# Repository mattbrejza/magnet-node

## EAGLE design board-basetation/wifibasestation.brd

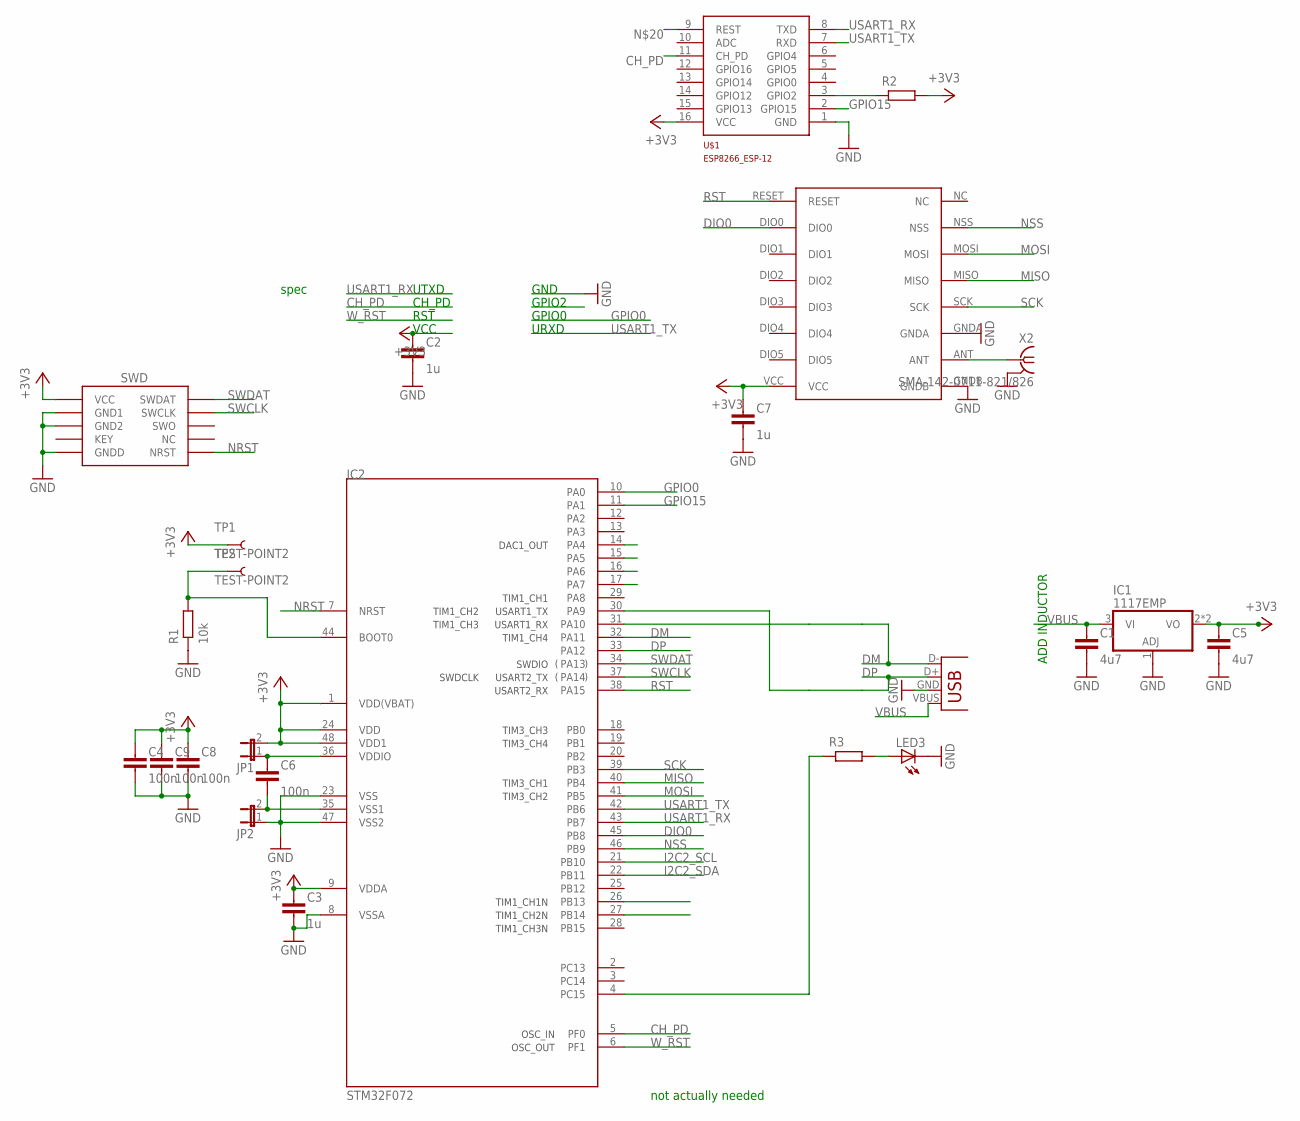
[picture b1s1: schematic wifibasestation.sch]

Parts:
C1: 4u7; C0603-N
C2, C3, C7: 1u; C0603-N
C4, C6, C8, C9: 100n; C0603-N
C5: 4u7; C0805-N
IC1: 1117EMP; SOT223
IC2: STM32F072; TQFP48
J1: SWD_SHROUD_SMD; SWD_SMD_SHROUD
JP1, JP2: JUMPER-2SMD-NC; SJ_2S
JP3: USB-A-H
LED3: LEDCHIP-LED0805; CHIP-LED0805
R1: 10k; R0603-N
R2, R3: RESISTOR0603-N; R0603-N
TP1, TP2: TEST-POINT2; PAD.02X.02
U$1: ESP8266_ESP-12; ESP8266-ESP12
U$2: RFM69HW; RFM
X2: SMA-142-0711-821/826; J502-ND-142-0711-821/826

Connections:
+3V3: C2.1, C3.1, C4.1, C5.1, C7.1, C8.1, C9.1, IC1.2 (VO), IC1.4 (VO), IC2.1 (VDD(VBAT)), IC2.9 (VDDA), IC2.24 (VDD), IC2.48 (VDD1), J1.1 (VCC), JP1.2, R2.2, TP1.P$1, U$1.16 (VCC), U$2.VCC
CH_PD: IC2.5 (PF0), U$1.11 (CH_PD)
DIO0: IC2.45 (PB8), U$2.DIO0
DM: IC2.31 (PA10), IC2.32 (PA11), JP3.D- (D+)
DP: IC2.30 (PA9), IC2.33 (PA12), JP3.D+ (D-)
GND: C1.2, C2.2, C3.2, C4.2, C5.2, C7.2, C8.2, C9.2, IC1.1 (ADJ), IC2.8 (VSSA), IC2.23 (VSS), IC2.47 (VSS2), J1.3 (GND1), J1.5 (GND2), J1.9 (GNDD), JP2.1, JP3.GND (VBUS), LED3.C, R1.1, U$1.1 (GND), U$2.GNDA, U$2.GNDB, X2.G@1 (2), X2.G@2 (2), X2.G@3 (2), X2.G@4 (2)
GPIO0: IC2.10 (PA0)
GPIO15: IC2.11 (PA1), U$1.2 (GPIO15)
I2C2_SCL: IC2.21 (PB10)
I2C2_SDA: IC2.22 (PB11)
MISO: IC2.40 (PB4), U$2.MISO
MOSI: IC2.41 (PB5), U$2.MOSI
unnamed: R2.1, U$1.3 (GPIO2)
unnamed: U$2.ANT, X2.1
unnamed: LED3.A, R3.2
unnamed: C6.1, IC2.36 (VDDIO), JP1.1
unnamed: C6.2, IC2.35 (VSS1), JP2.2
unnamed: IC2.44 (BOOT0), R1.2, TP2.P$1
unnamed: IC2.4 (PC15), R3.1
NRST: IC2.7 (NRST), J1.10 (NRST)
NSS: IC2.46 (PB9), U$2.NSS
RST: IC2.38 (PA15), U$2.RESET
SCK: IC2.39 (PB3), U$2.SCK
SWCLK: IC2.37 (PA14), J1.4 (SWCLK)
SWDAT: IC2.34 (PA13), J1.2 (SWDAT)
USART1_RX: IC2.43 (PB7), U$1.8 (TXD)
USART1_TX: IC2.42 (PB6), U$1.7 (RXD)
VBUS: C1.1, IC1.3 (VI), JP3.VBUS (GND)
W_RST: IC2.6 (PF1)

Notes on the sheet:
VCC
URXD
RST
CH_PD
UTXD
GPIO0
GPIO2
GND
not actually needed
spec
ADD INDUCTOR

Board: 2 copper layers, 24 parts (2 on the bottom side), 25 nets, no tracks yet.

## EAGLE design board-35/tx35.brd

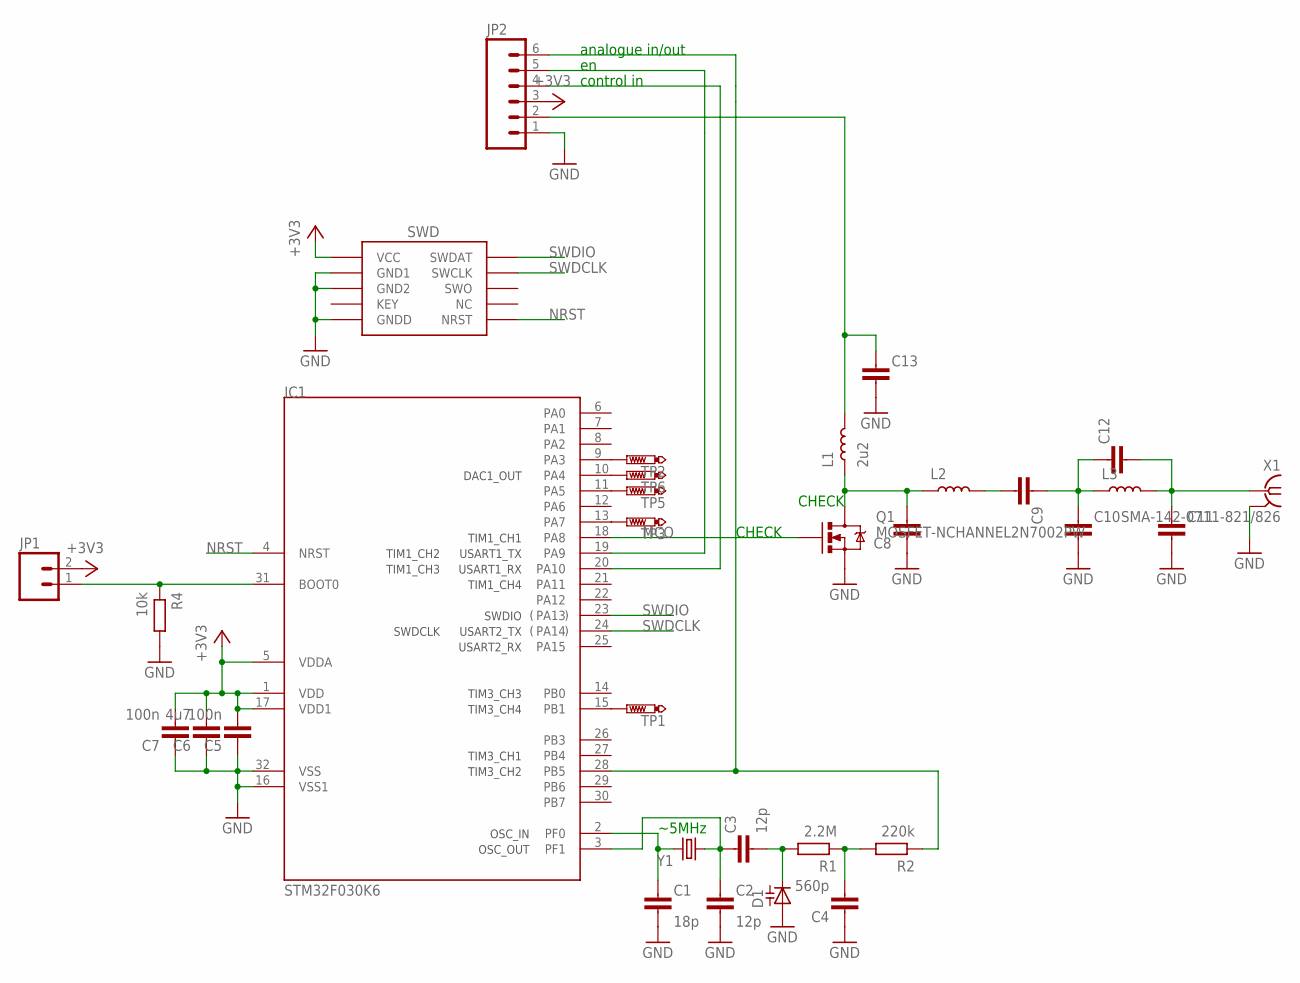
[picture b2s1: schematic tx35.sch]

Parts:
C1: 18p; C0603-N
C2, C3: 12p; C0603-N
C4: 560p; C0603-N
C5, C7: 100n; C0603-N
C6: 4u7; C0603-N
C8: CAPACITOR0603-N; C0603-N; FARNELL 2434613/2435457
C9, C10, C11, C12: CAPACITOR0603-N; C0603-N
C13: CAPACITOR0805-N; C0805-N
D1: DIODE_CAPACITANCE-SOD523; SOD523; FARNELL 1757783/(2443453)
IC1: STM32F030K6; TQFP32-08; FARNELL 2432085
J1: SWD_SHROUD; SWD_PTH_SHROUD
JP1: M02PTH; 1X02
JP2: M06SILK_FEMALE_PTH; 1X06
L1: 2u2; L0603-N; FARNELL 2215642
L2: INDUCTOR0603-N; L0603-N; FARNELL 1669538/(1711879)
L3: INDUCTOR0603-N; L0603-N
Q1: MOSFET-NCHANNEL2N7002PW; SOT323; FARNELL 1894713
R1: 2.2M; R0603-N
R2: 220k; R0603-N
R4: 10k; R0603-N
TP1, TP2, TP3, TP5, TP6: PTR1TP11R; TP11R
X1: SMA-142-0711-821/826; J502-ND-142-0711-821/826
Y1: CRYSTALHC49UV; HC49U-V; FARNELL 1666962/(1652566)

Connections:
+3V3: C5.2, C6.2, C7.2, IC1.1 (VDD), IC1.5 (VDDA), IC1.17 (VDD1), J1.1 (VCC), JP1.2, JP2.3
GND: C1.2, C2.2, C4.1, C5.1, C6.1, C7.1, C8.1, C10.2, C11.2, C13.2, D1.A, IC1.16 (VSS1), IC1.32 (VSS), J1.3 (GND1), J1.5 (GND2), J1.9 (GNDD), JP2.1, Q1.2 (S), R4.2, X1.G@1 (2), X1.G@2 (2), X1.G@3 (2), X1.G@4 (2)
MCO: IC1.18 (PA8), Q1.1 (G)
unnamed: C2.1, C3.1, IC1.3 (PF1), Y1.1
unnamed: C1.1, IC1.2 (PF0), Y1.2
unnamed: C3.2, D1.C, R1.2
unnamed: C4.2, R1.1, R2.2
unnamed: IC1.28 (PB5), JP2.6, R2.1
unnamed: C11.1, C12.2, L3.2, X1.1
unnamed: C13.1, JP2.2, L1.2
unnamed: C9.1, C10.1, C12.1, L3.1
unnamed: IC1.20 (PA10), JP2.4
unnamed: C9.2, L2.2
unnamed: C8.2, L1.1, L2.1, Q1.3 (D)
unnamed: IC1.19 (PA9), JP2.5
unnamed: IC1.31 (BOOT0), JP1.1, R4.1
unnamed: IC1.9 (PA3), TP2.TP
unnamed: IC1.15 (PB1), TP1.TP
unnamed: IC1.13 (PA7), TP3.TP
unnamed: IC1.11 (PA5), TP5.TP
unnamed: IC1.10 (PA4), TP6.TP
NRST: IC1.4 (NRST), J1.10 (NRST)
SWDCLK: IC1.24 (PA14), J1.4 (SWCLK)
SWDIO: IC1.23 (PA13), J1.2 (SWDAT)

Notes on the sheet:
~5MHz
CHECK
analogue in/out
control in

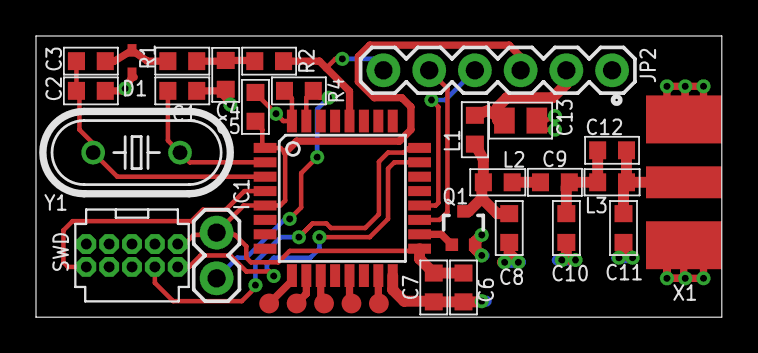
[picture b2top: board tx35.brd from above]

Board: 2 copper layers, 38.1 x 15.6 mm, 32 parts (0 on the bottom side), 24 nets.

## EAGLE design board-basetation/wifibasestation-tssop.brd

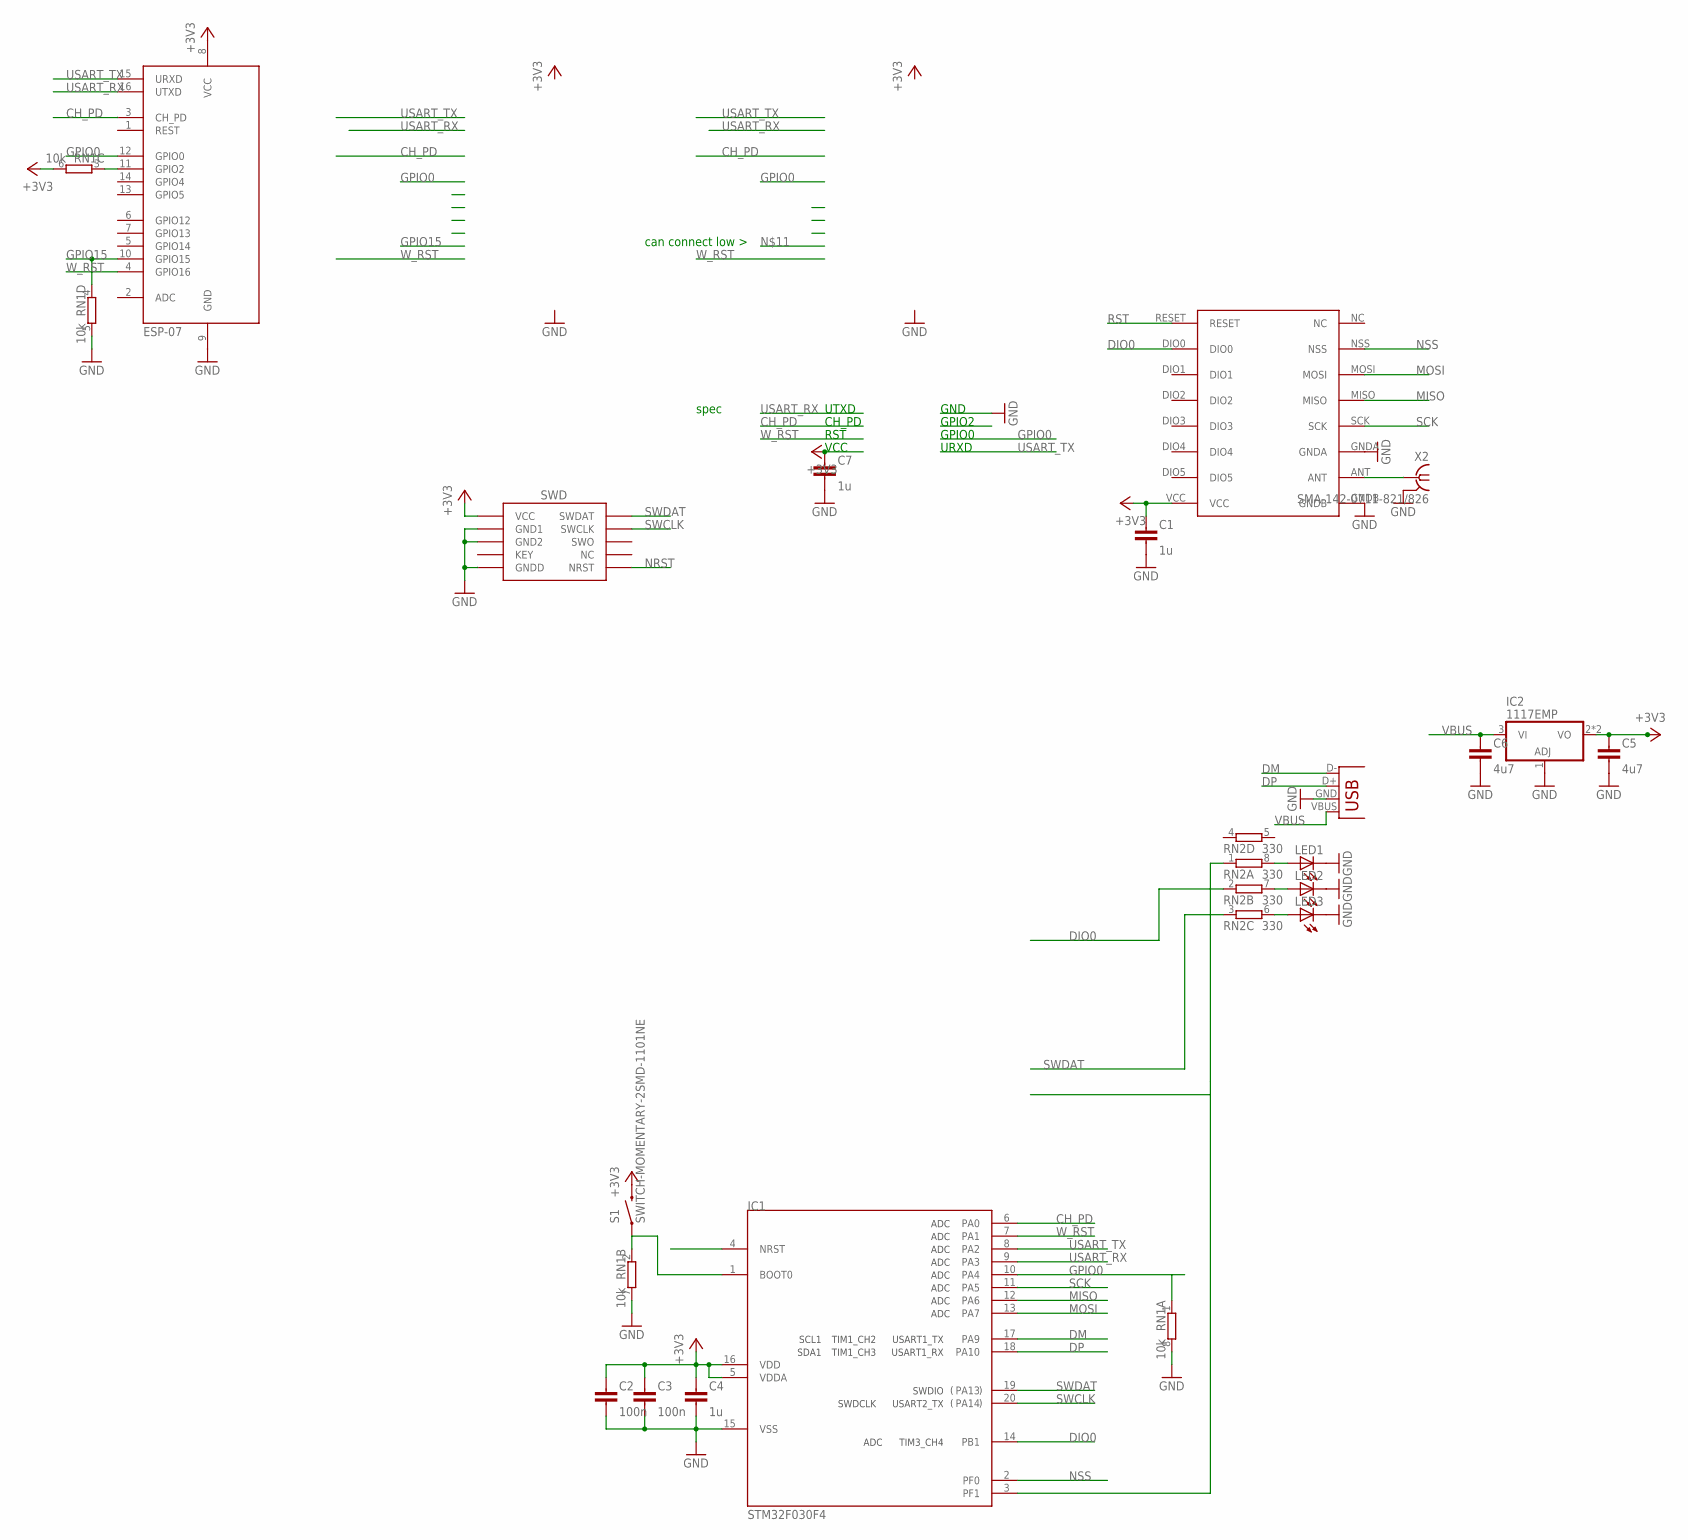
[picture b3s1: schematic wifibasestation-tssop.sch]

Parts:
C1, C4, C7: 1u; C0603-N
C2, C3: 100n; C0603-N
C5: 4u7; C0805-N
C6: 4u7; C0603-N
IC1: STM32F030F4; TSSOP20
IC2: 1117EMP; SOT223
J1: SWD_SHROUD_SMD; SWD_SMD_SHROUD
JP1: USB-A-H
LED1, LED2, LED3: LEDCHIP-LED0805; CHIP-LED0805
RN1: 10k; EXB38V
RN2: 330; EXB38V
S1: SWITCH-MOMENTARY-2SMD-1101NE; TACTILE-SWITCH-1101NE
U$1: RFM69HW; RFM
X1: ESP-07
X2: SMA-142-0711-821/826; J502-ND-142-0711-821/826

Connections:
+3V3: C1.1, C2.1, C3.1, C4.1, C5.1, C7.1, IC1.5 (VDDA), IC1.16 (VDD), IC2.2 (VO), IC2.4 (VO), J1.1 (VCC), RN1.6 (2), S1.2, U$1.VCC, X1.8 (VCC)
CH_PD: IC1.6 (PA0), X1.3 (CH_PD)
DIO0: IC1.14 (PB1), RN2.2 (1), U$1.DIO0
DM: IC1.17 (PA9), JP1.D- (D+)
DP: IC1.18 (PA10), JP1.D+ (D-)
GND: C1.2, C2.2, C3.2, C4.2, C5.2, C6.2, C7.2, IC1.15 (VSS), IC2.1 (ADJ), J1.3 (GND1), J1.5 (GND2), J1.9 (GNDD), JP1.GND (VBUS), LED1.C, LED2.C, LED3.C, RN1.5 (2), RN1.7 (2), RN1.8 (2), U$1.GNDA, U$1.GNDB, X1.9 (GND), X2.G@1 (2), X2.G@2 (2), X2.G@3 (2), X2.G@4 (2)
GPIO0: IC1.10 (PA4), RN1.1, X1.12 (GPIO0)
GPIO15: RN1.4 (1), X1.10 (GPIO15)
MISO: IC1.12 (PA6), U$1.MISO
MOSI: IC1.13 (PA7), U$1.MOSI
unnamed: IC1.1 (BOOT0), RN1.2 (1), S1.1
unnamed: U$1.ANT, X2.1
unnamed: RN1.3 (1), X1.11 (GPIO2)
unnamed: LED1.A, RN2.8 (2)
unnamed: LED2.A, RN2.7 (2)
unnamed: LED3.A, RN2.6 (2)
unnamed: IC1.3 (PF1), RN2.1
NRST: IC1.4 (NRST), J1.10 (NRST)
NSS: IC1.2 (PF0), U$1.NSS
RST: U$1.RESET
SCK: IC1.11 (PA5), U$1.SCK
SWCLK: IC1.20 (PA14), J1.4 (SWCLK)
SWDAT: IC1.19 (PA13), J1.2 (SWDAT), RN2.3 (1)
USART_RX: IC1.9 (PA3), X1.16 (UTXD)
USART_TX: IC1.8 (PA2), X1.15 (URXD)
VBUS: C6.1, IC2.3 (VI), JP1.VBUS (GND)
W_RST: IC1.7 (PA1), X1.4 (GPIO16)

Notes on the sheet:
VCC
URXD
RST
CH_PD
UTXD
GPIO0
GPIO2
GND
spec
can connect low >

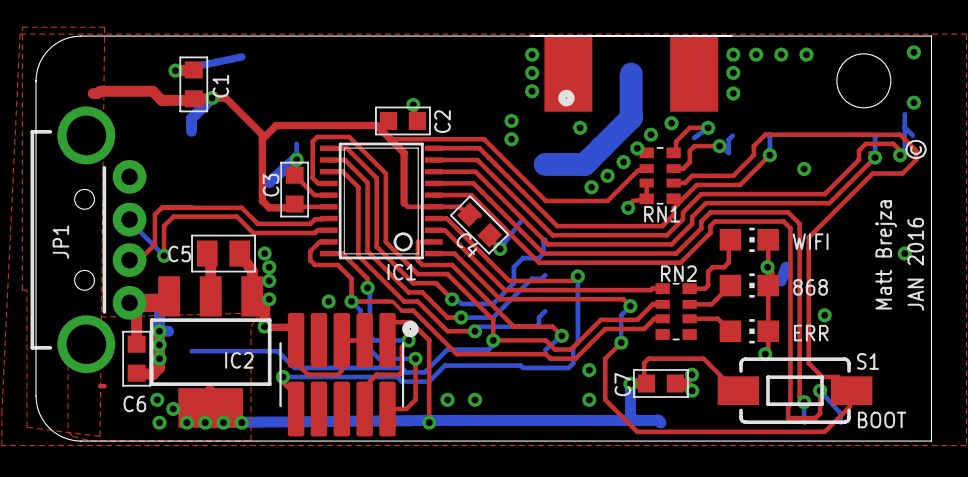
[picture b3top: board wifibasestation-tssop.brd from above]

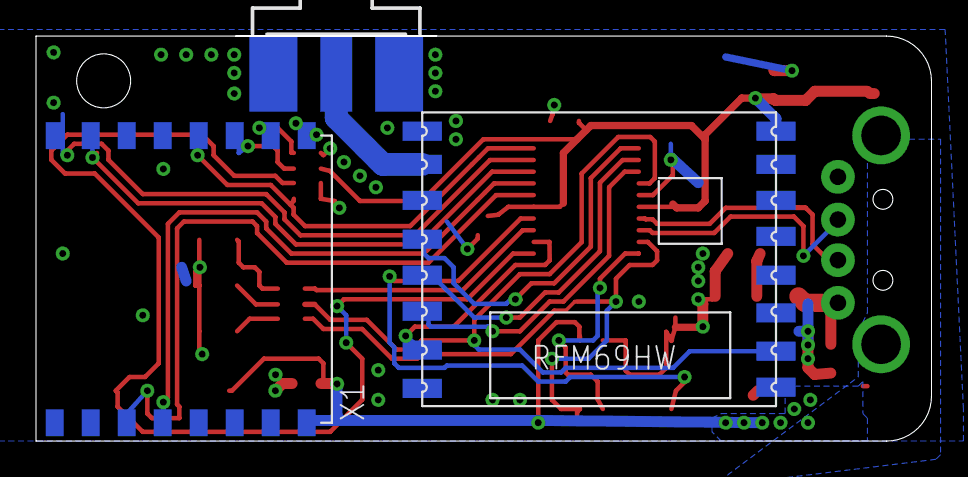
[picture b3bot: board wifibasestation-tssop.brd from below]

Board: 2 copper layers, 49.8 x 22.5 mm, 20 parts (3 on the bottom side), 26 nets.

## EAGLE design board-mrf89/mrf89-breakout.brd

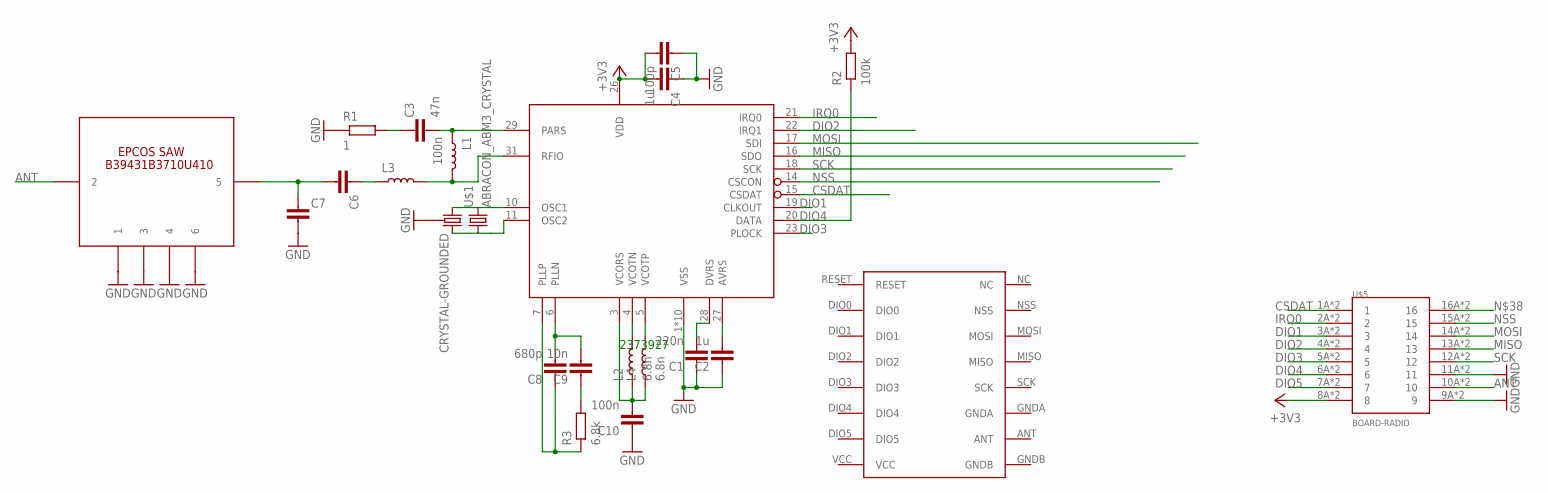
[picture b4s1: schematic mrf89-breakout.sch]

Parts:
C1: 220n; C0603-N
C2, C4: 1u; C0603-N
C3: 47n; C0603-N
C5: 100p; C0603-N
C6, C7: CAPACITOR0603-N; C0603-N
C8: 680p; C0603-N
C9: 10n; C0603-N
C10: 100n; C0603-N
IC1: MRF89XA; QFN32
L1: 100n; L0603-N
L2, L4: 6.8n; L0402-N
L3: INDUCTOR0402-N; L0402-N
R1: 1; R0603-N
R2: 100k; R0603-N
R3: 6.8k; R0603-N
U$1: ABRACON_ABM3_CRYSTAL
U$2: EPCOS_SAW_FILTER
U$3: RFM69HW; RFM
U$4: CRYSTAL-GROUNDED; CRYSTAL-SMD-5X3
U$5: BOARD-RADIO

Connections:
+3V3: C4.2, C5.2, IC1.26 (VDD), R2.2, U$5.8A (8), U$5.8B (8)
ANT: U$2.P$2 (2), U$5.10A (10), U$5.10B (10)
CSDAT: IC1.15 (CSDAT), U$5.1A (1), U$5.1B (1)
DIO1: IC1.19 (CLKOUT), U$5.3A (3), U$5.3B (3)
DIO2: IC1.22 (IRQ1), U$5.4A (4), U$5.4B (4)
DIO3: IC1.23 (PLOCK), U$5.5A (5), U$5.5B (5)
DIO4: IC1.20 (DATA), R2.1, U$5.6A (6), U$5.6B (6)
DIO5: U$5.7A (7), U$5.7B (7)
GND: C1.1, C2.1, C4.1, C5.1, C7.2, C10.1, IC1.1 (VSS), IC1.2 (VSS), IC1.8 (VSS), IC1.9 (VSS), IC1.12 (VSS), IC1.24 (VSS), IC1.25 (VSS), IC1.30 (VSS), IC1.32 (VSS), IC1.EXP (VSS), R1.1, U$2.P$1 (1), U$2.P$3 (3), U$2.P$4 (4), U$2.P$6 (6), U$4.2 (3), U$4.4 (3), U$5.9A (9), U$5.9B (9), U$5.11A (11), U$5.11B (11)
IRQ0: IC1.21 (IRQ0), U$5.2A (2), U$5.2B (2)
MISO: IC1.16 (SDO), U$5.13A (13), U$5.13B (13)
MOSI: IC1.17 (SDI), U$5.14A (14), U$5.14B (14)
unnamed: C1.2, IC1.28 (DVRS)
unnamed: C2.2, IC1.27 (AVRS)
unnamed: C3.2, IC1.29 (PARS), L1.1
unnamed: IC1.31 (RFIO), L1.2, L3.2
unnamed: C6.1, L3.1
unnamed: C6.2, C7.1, U$2.P$5 (5)
unnamed: C8.1, IC1.7 (PLLP), R3.1
unnamed: C8.2, C9.2, IC1.6 (PLLN)
unnamed: C9.1, R3.2
unnamed: IC1.4 (VCOTN), L2.2
unnamed: IC1.5 (VCOTP), L4.2
unnamed: C10.2, IC1.3 (VCORS), L2.1, L4.1
unnamed: C3.1, R1.2
unnamed: IC1.10 (OSC1), U$1.P$2 (2), U$4.3 (1)
unnamed: IC1.11 (OSC2), U$1.P$1 (1), U$4.1 (2)
unnamed: U$5.16A (16), U$5.16B (16)
NSS: IC1.14 (CSCON), U$5.15A (15), U$5.15B (15)
SCK: IC1.18 (SCK), U$5.12A (12), U$5.12B (12)

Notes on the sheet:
2373927

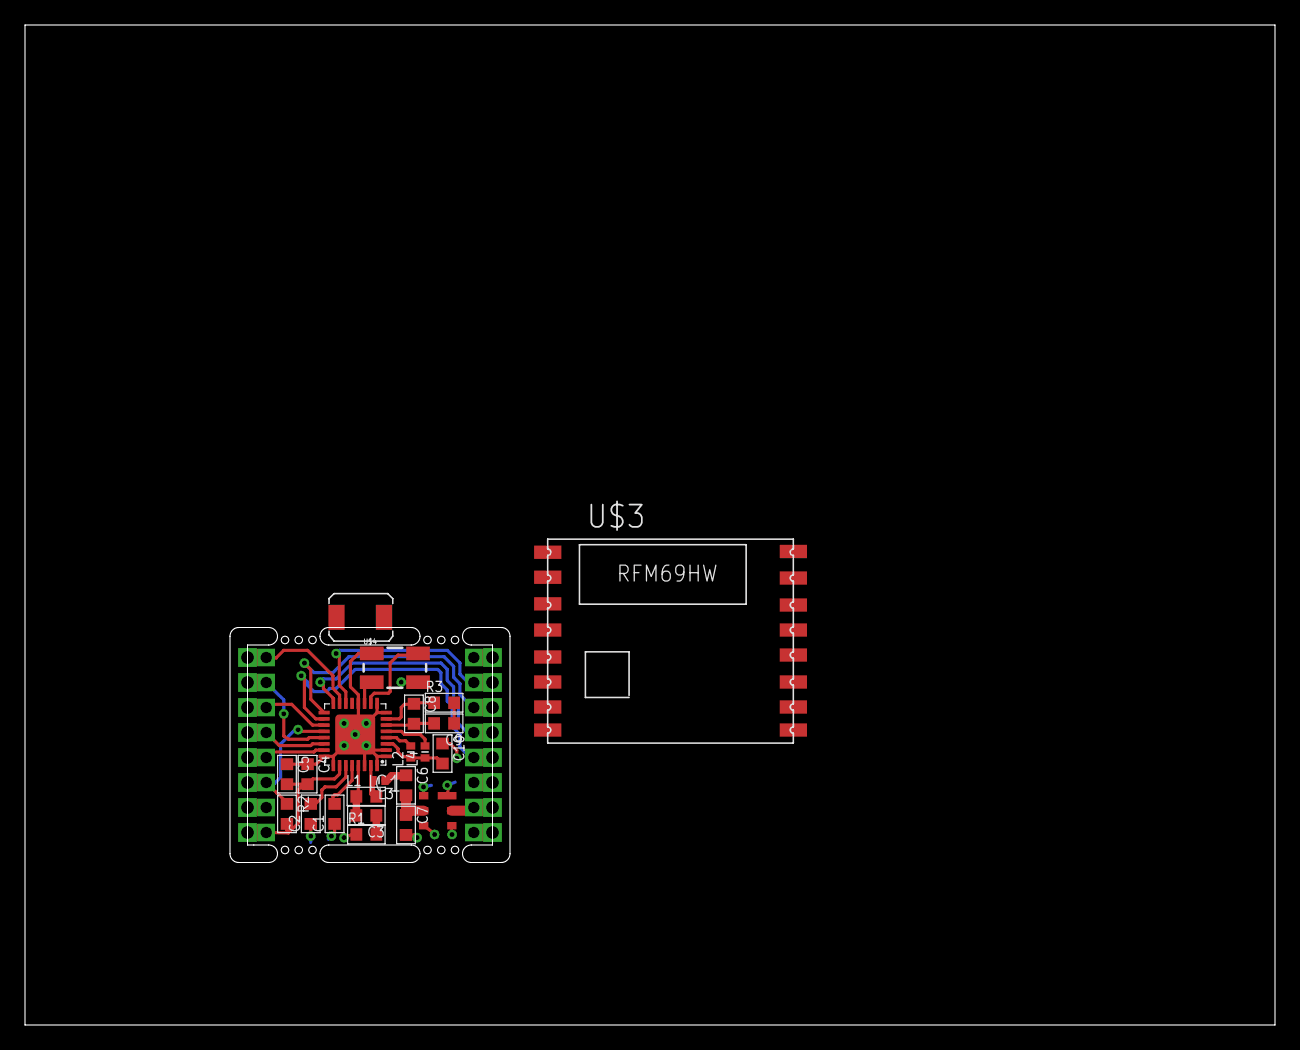
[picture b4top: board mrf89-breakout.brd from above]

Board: 2 copper layers, 100.0 x 80.0 mm, 24 parts (0 on the bottom side), 30 nets.

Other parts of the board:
U$6: BOARD-RADIO-CUTOUT

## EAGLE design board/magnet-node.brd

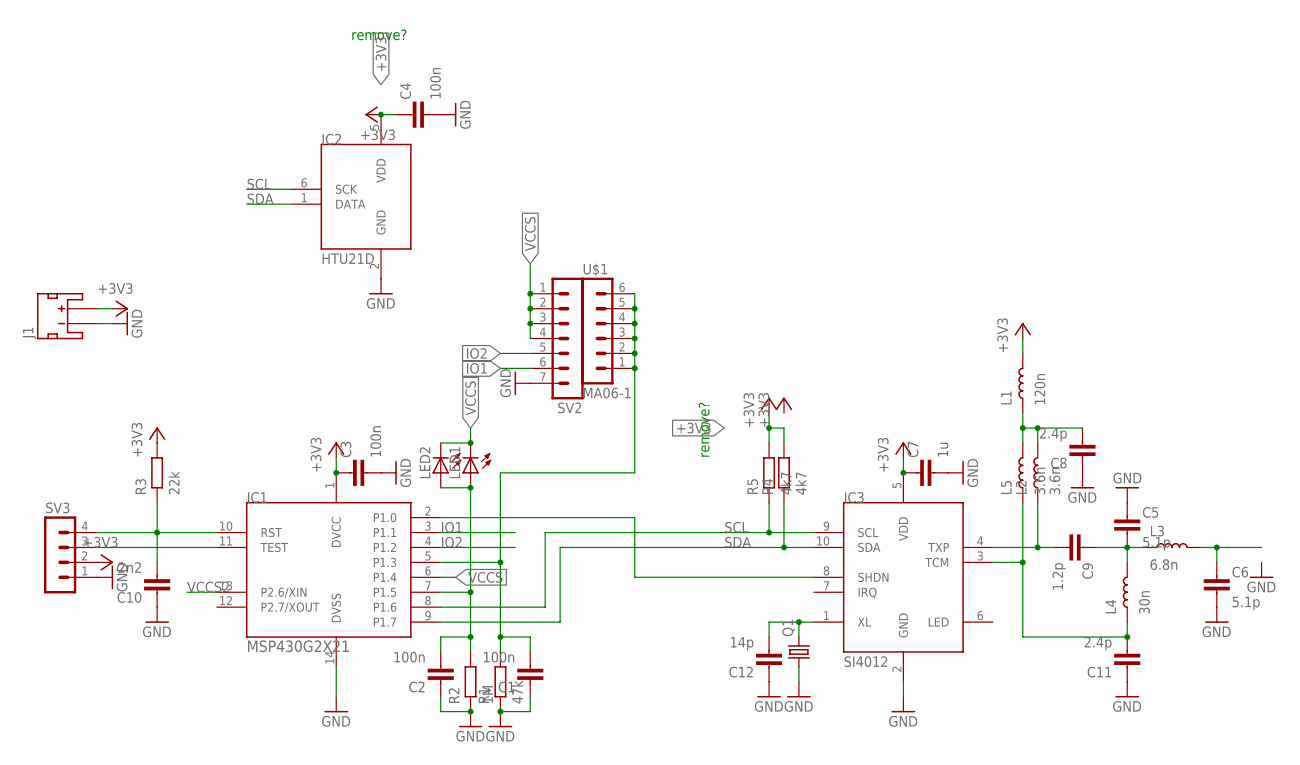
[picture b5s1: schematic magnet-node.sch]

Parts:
C1, C2, C3, C4: 100n; C0603-N
C5, C6: 5.1p; C0603-N
C7: 1u; C0603-N
C8, C11: 2.4p; C0603-N
C9: 1.2p; C0603-N
C10: 2n2; C0603-N
C12: 14p; C0603-N
IC1: MSP430G2X21; TSSOP14
IC2: HTU21D; DFN6-L
IC3: SI4012; MSOP10
J1: JST_2MM_MALE_TH; JST-2-TH
L1: 120n; L0603-N
L2, L5: 3.6n; L0402-N
L3: 6.8n; L0402-N
L4: 30n; L0402-N
LED1, LED2: LEDSMT1206; 1206
Q1: CRYSTALHC49S; HC49/S
R1: 47k; R0603-N
R2: 1M; R0603-N
R3: 22k; R0603-N
R4, R5: 4k7; R0603-N
SV2: MA07-1S; MA07-1-SMD
SV3: MA04-1E; EDGE_4
U$1: MA06-1; MA06-1-SMD

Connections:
+3V3: C3.1, C4.1, C7.1, IC1.1 (DVCC), IC2.5 (VDD), IC3.5 (VDD), J1.1 (+), L1.2, R3.2, R4.2, R5.2, SV3.2
GND: C1.1, C2.1, C3.2, C4.2, C5.1, C6.2, C7.2, C8.1, C10.1, C11.1, C12.1, IC1.14 (DVSS), IC2.2 (GND), IC3.2 (GND), J1.2 (-), Q1.1, R1.1, R2.1, SV2.7, SV3.1
IO1: IC1.3 (P1.1), SV2.6
IO2: IC1.4 (P1.2), SV2.5
unnamed: IC1.2 (P1.0), IC3.8 (SHDN)
unnamed: IC1.11 (TEST), SV3.3
unnamed: C8.2, L1.1, L2.2, L5.2
unnamed: C12.2, IC3.1 (XL), Q1.2
unnamed: C5.2, C9.1, L3.1, L4.2
unnamed: C11.2, IC3.3 (TCM), L4.1, L5.1
unnamed: C9.2, IC3.4 (TXP), L2.1
unnamed: C6.1, L3.2
unnamed: C1.2, IC1.5 (P1.3), R1.2, U$1.1, U$1.2, U$1.3, U$1.4, U$1.5, U$1.6
unnamed: C2.2, IC1.7 (P1.5), LED1.A, LED2.A, R2.2
unnamed: C10.2, IC1.10 (RST), R3.1, SV3.4
SCL: IC1.8 (P1.6), IC2.6 (SCK), IC3.9 (SCL), R5.1
SDA: IC1.9 (P1.7), IC2.1 (DATA), IC3.10 (SDA), R4.1
VCCS: IC1.6 (P1.4), LED1.C, LED2.C, SV2.1, SV2.2, SV2.3, SV2.4
VCCS2: IC1.13 (P2.6/XIN)

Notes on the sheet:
remove?

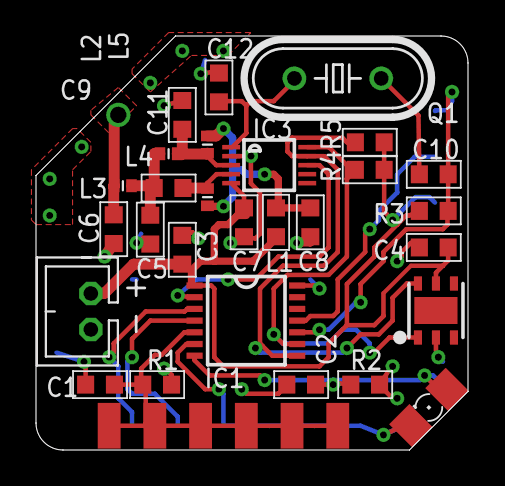
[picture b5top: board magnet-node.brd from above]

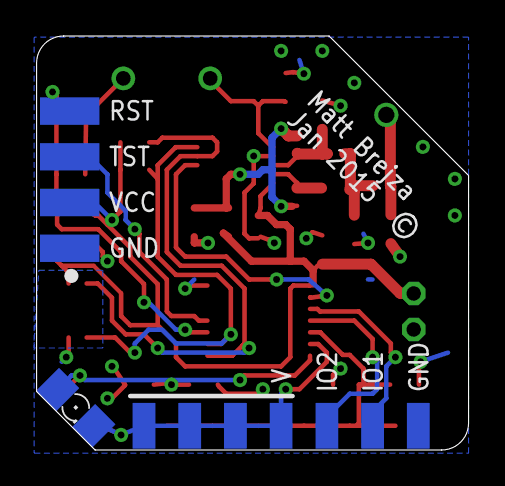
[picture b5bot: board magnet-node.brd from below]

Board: 2 copper layers, 24.0 x 23.0 mm, 32 parts (3 on the bottom side), 18 nets.

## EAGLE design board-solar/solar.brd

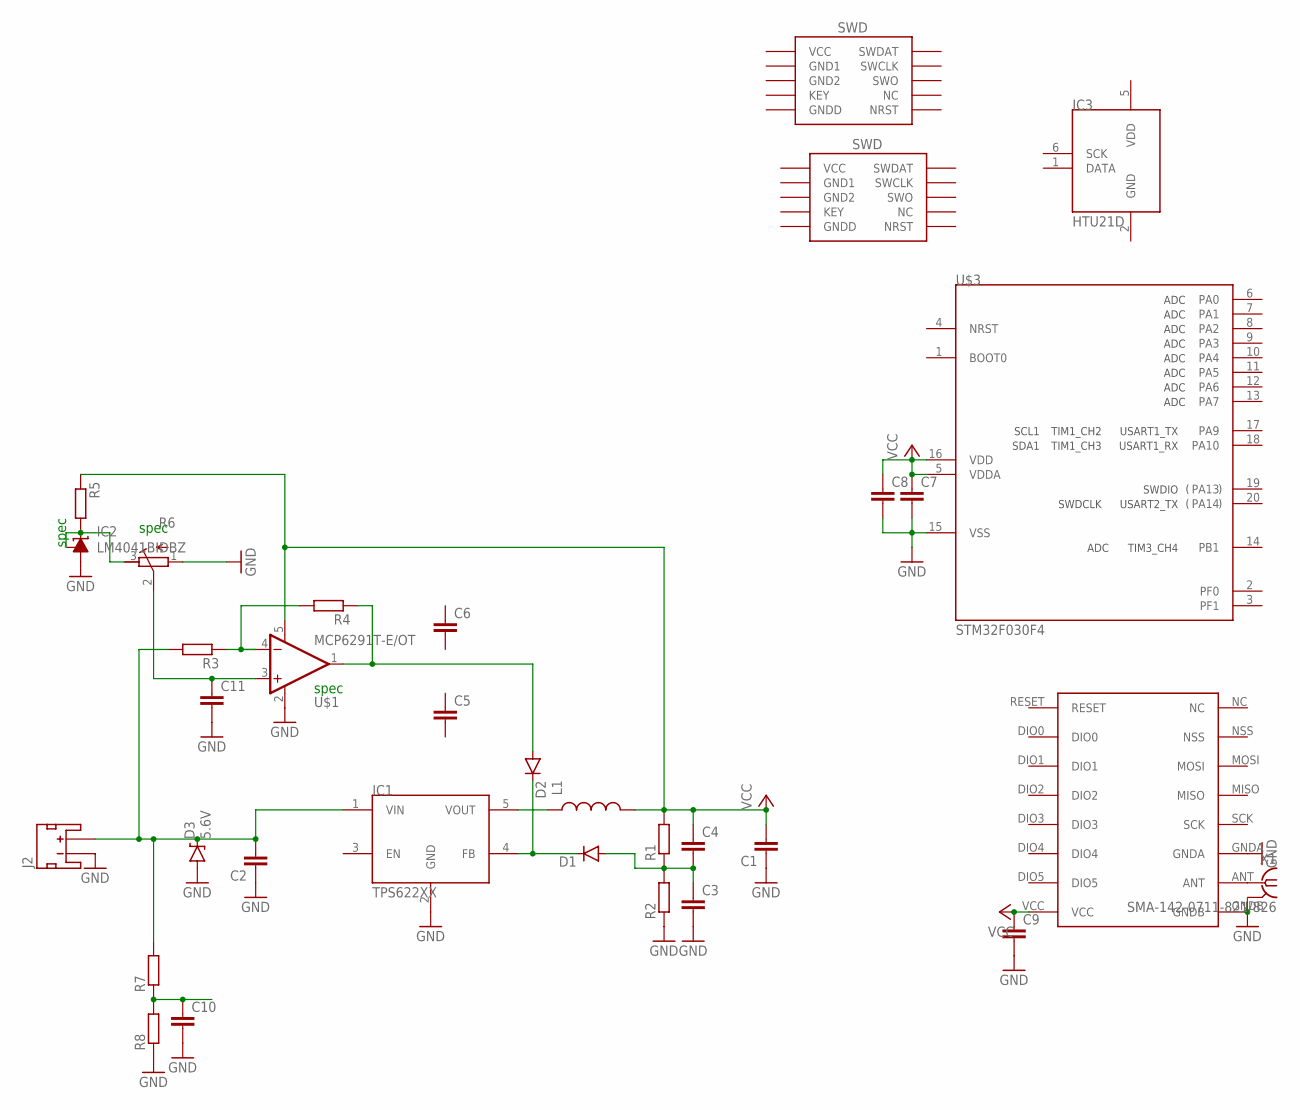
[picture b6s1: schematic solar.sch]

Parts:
C1, C2: C-EUC0805; C0805
C3, C4, C5, C6, C7, C8, C9, C10, C11: C-EUC0603; C0603
D1, D2: 250mA/100V; SOD-323
D3: 5.6V; SOD-323
IC1: TPS622XX; SOT23-5L
IC2: LM4041BIDBZ; DBZ_R-PDSO-G3
IC3: HTU21D; DFN6-L
J1: SWD_SHROUD_SMD; SWD_SMD_SHROUD
J2: JST_2MM_MALE; JST-2-SMD
J3: SWD_SHROUD; SWD_PTH_SHROUD
L1: INDUCTOR1007; 1007
R1, R2, R3, R4, R5, R7, R8: R-EU_R0603; R0603
R6: R-TRIMM3103; RTRIM3103
U$1: MCP6291T-E/OT; SOT23-5
U$3: STM32F030F4; TSSOP20
U$4: RFM69HW; RFM
X1: SMA-142-0711-821/826; J502-ND-142-0711-821/826

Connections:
GND: C1.1, C2.1, C3.2, C7.2, C8.2, C9.2, C10.2, C11.2, D3.A, IC1.2 (GND), IC2.3 (A), J2.1 (-), R2.1, R6.1 (E), R8.1, U$1.2 (V-), U$3.15 (VSS), U$4.GNDA, U$4.GNDB, X1.G@1 (2), X1.G@2 (2), X1.G@3 (2), X1.G@4 (2)
GND1: J1.3 (GND1), J3.3 (GND1)
GND2: J1.5 (GND2), J3.5 (GND2)
GNDD: J1.9 (GNDD), J3.9 (GNDD)
unnamed: C3.1, C4.2, D1.A, R1.1, R2.2
unnamed: IC1.5 (VOUT), L1.1
unnamed: D1.C, D2.C, IC1.4 (FB)
unnamed: C2.2, D3.C, IC1.1 (VIN), J2.2 (+), R3.2, R7.2
unnamed: D2.A, R4.1, U$1.1 (OUT)
unnamed: R3.1, R4.2, U$1.4 (-IN)
unnamed: C11.1, R6.2 (S), U$1.3 (+IN)
unnamed: U$4.ANT, X1.1
unnamed: IC2.1 (FB), IC2.2 (C), R5.2, R6.3 (A)
unnamed: C10.1, R7.1, R8.2
VCC: C1.2, C4.1, C7.1, C8.1, C9.1, J1.1 (VCC), J3.1 (VCC), L1.2, R1.2, R5.1, U$1.5 (V+), U$3.5 (VDDA), U$3.16 (VDD), U$4.VCC

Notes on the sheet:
spec

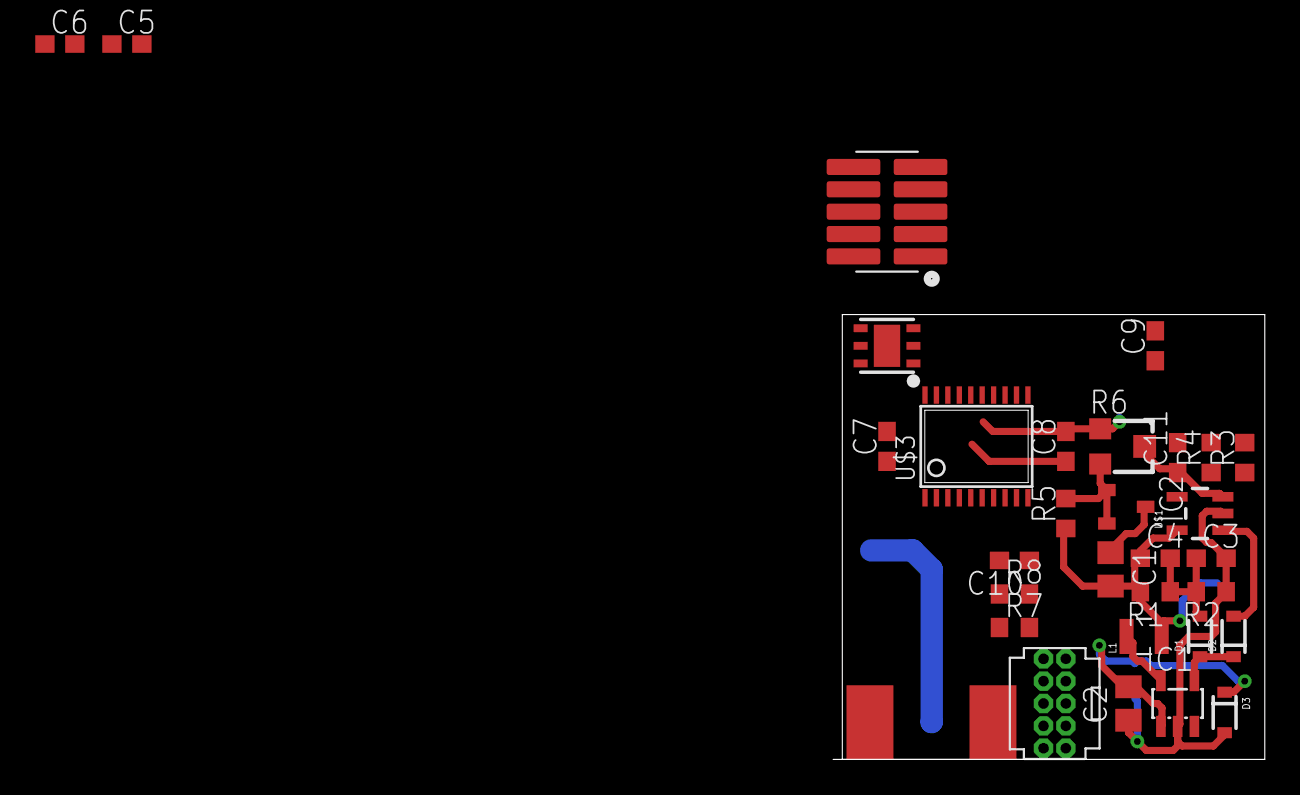
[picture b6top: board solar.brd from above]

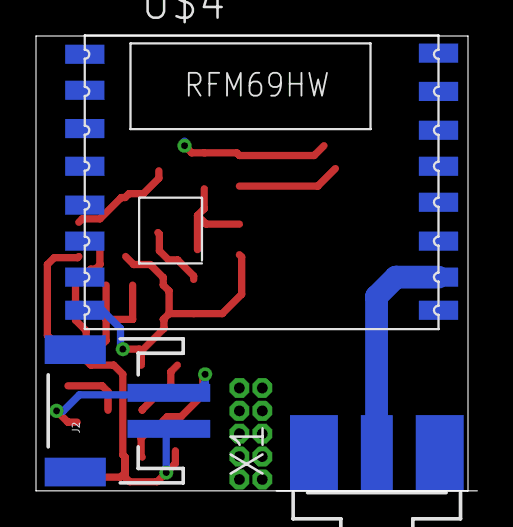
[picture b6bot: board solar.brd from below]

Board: 2 copper layers, 24.5 x 25.3 mm, 33 parts (3 on the bottom side), 15 nets.

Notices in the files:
parts and their libraries:
SparkFun-FreqCtrl: Licensing: Creative Commons ShareAlike 4.0 International - https://creativecommons.org/licenses/by-sa/4.0
SparkFun-Connectors: Licensing: CC v3.0 Share-Alike You are welcome to use this library for commercial purposes.
